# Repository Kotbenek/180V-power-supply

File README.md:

# Moved to Codeberg

This repository was moved to Codeberg:
https://codeberg.org/Kotbenek/180V-power-supply

# 180V-power-supply
180V power supply PCB used in my Nixie clock

## Board overview
- Designed for rectified, smoothed 12V AC input (around 16V DC)
- 180V DC output

## Images

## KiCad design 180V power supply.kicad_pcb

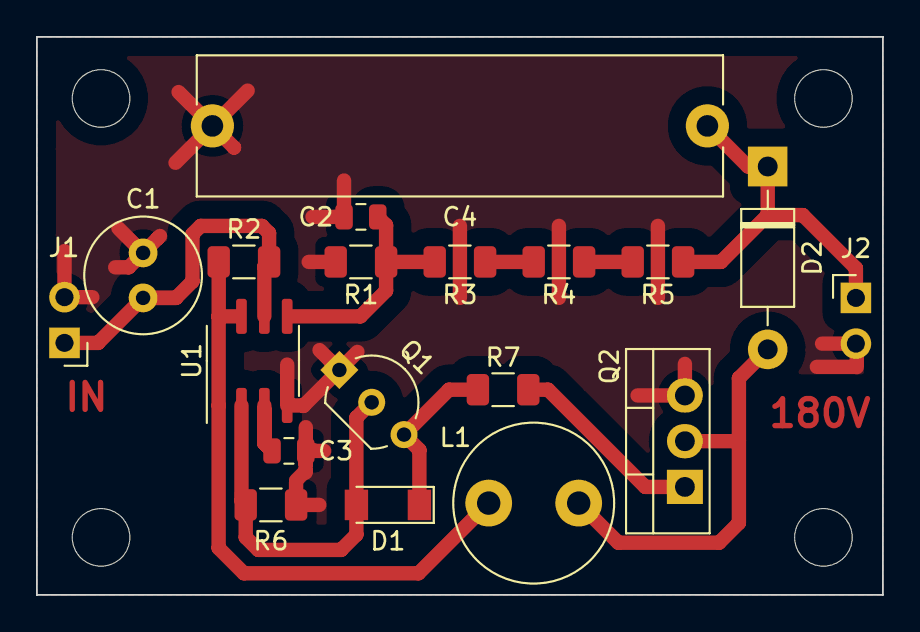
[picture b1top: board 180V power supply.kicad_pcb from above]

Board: 2 copper layers, 47.0 x 31.0 mm, 23 parts (0 on the bottom side), 12 nets.

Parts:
3mm hole, 3mm hole#2, 3mm hole#3, 3mm hole#4: MountingHole_3.2mm_M3_DIN965
C1: 100u; C_Radial_D6.3mm_H11.0mm_P2.50mm
C2, C3: 1n; C_0805_2012Metric
C4: 3u3; C_Rect_L29.0mm_W7.6mm_P27.50mm_MKT
D1: LL4148; D_MiniMELF
D2: UF4007; D_DO-41_SOD81_P10.16mm_Horizontal
J1: Input; PinHeader_1x02_P2.54mm_Horizontal
J2: 180V; PinHeader_1x02_P2.54mm_Horizontal
L1: 470u; L_Radial_D8.7mm_P5.00mm_Fastron_07HCP
Q1: BC557; TO-92_Inline_Wide
Q2: IRF740; TO-220-3_Vertical
R1: 10k; R_1206_3216Metric
R2: R22; R_1206_3216Metric
R3, R4: 220k; R_1206_3216Metric
R5: 1M; R_1206_3216Metric
R6: 1k; R_1206_3216Metric
R7: 22; R_1206_3216Metric
U1: MC34063AD; SOIC-8_3.9x4.9mm_P1.27mm

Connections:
GND: C1.2, C2.2, C3.2, C4.2, J1.2, J2.2, Q1.1, Q2.3, R1.2, R6.2, U1.4
unnamed: C1.1, J1.1, R2.2, U1.6
unnamed: C2.1, R1.1, R3.2, U1.5
unnamed: C3.1, U1.3
unnamed: C4.1, D2.1, J2.1, R5.1
unnamed: D1.1, Q1.3, R7.2
unnamed: D1.2, Q1.2, R6.1, U1.2
unnamed: D2.2, L1.2, Q2.2
unnamed: L1.1, R2.1, U1.1, U1.7, U1.8
unnamed: Q2.1, R7.1
unnamed: R3.1, R4.2
unnamed: R4.1, R5.2

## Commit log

2020-11-26 Version 1.0
2020-11-26 Created README.md
2020-11-26 Added pcb image without components
2020-11-26 Added sheet info for board
2020-11-26 Added schematic as pdf file
2020-11-30 Fixed J1 and J2 silkscreen hanging outside PCB edges
2020-11-30 Fixed two images being too small
2021-02-05 Minor fixes
2021-04-22 Added LICENSE.md
2021-09-03 Added missing gerber files
2024-09-25 LICENSE.md: Change line breaks from CRLF to LF
2024-09-25 LICENSE.md: Update date
2025-08-17 Moved to Codeberg
